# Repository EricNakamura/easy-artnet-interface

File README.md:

# easy-artnet-interface
A open-source project aiming to give access to all people a low budget and easy-to-use artnet-dmx interface node

# 🎭 Professional WT32-ETH01 Art-Net to DMX Node

Um Node Art-Net para DMX512 de alta performance e nível industrial, desenvolvido para a placa **WT32-ETH01 (ESP32 Ethernet)**. 

Este projeto resolve os problemas clássicos de rede em eventos ao vivo: não perde a ligação à internet no seu computador (Mac/Windows), possui **DHCP Inteligente com Auto-Router**, suporte **mDNS**, **proteção contra apagão DMX (40Hz constante)** e **Reset de Fábrica sem botões**.

## 📁 Estrutura do Repositório

| Pasta | Conteúdo |
| :--- | :--- |
| `firmware/` | Sketches por variante de hardware (WT32-ETH01 e ESP32 + W5500) |
| `hub/` | Hub local Rust (descoberta + proxy do painel); ver [hub/README.md](hub/README.md) |
| `src/` | Entradas do PlatformIO; não editar |
| `hardware/kicad/` | Esquema e PCB KiCad |
| `hardware/cad/` | Modelos FreeCAD da caixa |
| `scripts/` | Upload e recuperação por USB |
| `docs/` | [Diagnóstico](docs/diagnostics.md), [recuperação](docs/recovery.md) e [protótipo](docs/prototype.md) |

---

## 🚀 Principais Características

* **Ethernet Fiável:** Baseado no chip LAN8720 (ligação por cabo super estável via UDP).
* **DHCP Inteligente com Auto-Router:**
  * Se ligado a um Router/Switch: obtém IP automaticamente via DHCP.
  * Se ligado direto ao PC/Mac (sem router): **a placa transforma-se num Servidor DHCP automático** (Gama `10.0.0.x`), permitindo ligação imediata *Plug & Play*.
* **Sem Conflito de Internet:** O servidor DHCP interno da placa desativa o envio de Gateway/DNS, permitindo que o Mac/PC continue a usar o Wi-Fi para aceder à internet (WhatsApp, navegação, etc.) enquanto controla a iluminação por cabo.
* **Acesso por Nome (mDNS):** Aceda ao painel via `http://dmx-xxxxxx.local` (o sufixo único aparece no serial e no próprio painel; também pode usar o IP mostrado no painel).
* **Hub local (MVP):** app Rust descobre a interface por mDNS/beacon/scan e abre o painel em `http://localhost:8080/d/<id>/`, sem `.local`/cloud; inclui claim code + HMAC no painel. Ver [hub/README.md](hub/README.md).
* **Painel Web de Configuração:** Interface responsiva para alterar Universo Art-Net, alternar entre DHCP e IP Fixo.
* **Proteção DMX Contínua (40 FPS / 25ms):** Se a rede falhar ou o software de luz fechar, o ESP32 continua a enviar a última cena DMX aos aparelhos, evitando apagões ou piscadelas no palco.
* **Smart Factory Reset:** Reset de fábrica por ciclo de energia (ligar/desligar a placa 2 vezes seguidas rapidamente), eliminando a necessidade de botões físicos.
* **Logging Profissional:** Utiliza o sistema de logs nativo do ESP32 (`log_i`, `log_w`, `log_e`), eliminando o consumo de CPU em produção.

---

## 🛠️ Esquema de Hardware & Pinos

### Componentes Necessários
1. Módulo **WT32-ETH01** (ESP32 com Ethernet).
2. Transcetor RS-485: **Módulo MAX485 padrão** (usado e validado neste projeto).
3. Fêmea XLR 3 pinos ou 5 pinos.
4. Fonte de alimentação 5V DC ou conector USB de escolha.
5. (opcional) Programador esp32 cp2102

> [!WARNING]
> **SOBRE O MÓDULO RS-485**
> O esquema de ligações abaixo foi desenhado e testado especificamente para o **módulo MAX485 clássico**. Se optar por utilizar outros chips (como o SN75176) ou módulos RS-485 isolados de nível industrial, **precisará de adaptar as ligações físicas**. Alguns módulos isolados gerem o sinal de *Enable* automaticamente, o que significa que o pino `EN` (IO04) do ESP32 poderá ter de ser ignorado ou ligado de forma diferente no seu hardware.

### Conexões (WT32-ETH01 ↔ Transcetor MAX485)

| Sinal | Pino WT32-ETH01 | Pino MAX485 | Descrição |
| :--- | :--- | :--- | :--- |
| **TX** | `TXD` | DI (Data In) | Transmissão de dados DMX |
| **EN** | `IO04` | DE / RE | Enable (Habilitar Transmissão) |
| **RX** | `RXD` | RO (Receiver Out)| Reservado / Leitura |
| **VCC** | `5V` | VCC | Alimentação 5V |
| **GND** | `GND` | GND | Terra |

> **Conexão DMX (Saída XLR):** 
> * MAX485 **A** ➔ XLR Pino 3 (DMX +)  
> * MAX485 **B** ➔ XLR Pino 2 (DMX -)  
> * MAX485 **GND** ➔ XLR Pino 1 (Shield / Terra)

---

## 💻 Como Compilar e Enviar o Código

### PlatformIO (recomendado)

O `platformio.ini` já define um ambiente por variante:

| Ambiente | Hardware | Core ESP32 |
| :--- | :--- | :--- |
| `w5500_sem_int` | ESP32 + W5500 (sem fio INT) | 3.x |
| `w5500_com_int` | ESP32 + W5500 (INT no GPIO27) | 2.0.17 |
| `wt32_eth01` | WT32-ETH01 (LAN8720) | 2.0.17 |
| `w5500_diag` | Diagnóstico do W5500 | 3.x |

```bash
pio run -e w5500_sem_int -t upload
pio device monitor
```

### Requisitos (Arduino IDE)

> [!IMPORTANT]
> **VERSÃO DO CORE DO ESP32 OBRIGATÓRIA**
> Este projeto manipula o núcleo de rede a baixo nível para criar o Servidor DHCP. O código foi construído e otimizado para o **ESP32 Core versão 2.x (recomenda-se a 2.0.17)**. 
> Instalar a versão 3.x mais recente no *Boards Manager* causará erros de compilação na variável `dhcps_offer_option`.

1. Instalar o suporte para **ESP32** na Arduino IDE via Boards Manager (`esp32` by Espressif Systems).
2. Selecionar a placa: **ESP32 Dev Module**.
3. Definir a partição de memória: `Huge APP` ou `Default 4MB with spiffs`.
4. **Bibliotecas Externas Necessárias:**
   * `esp_dmx` (por Mitch Weiss) - *Utilizar a versão mais recente.*
   * `ArtnetWifi` (por Hideaki Tai) - *Utilizar a versão mais recente.*

### Configuração do Debug / Logs
Em **Ferramentas (Tools) > Core Debug Level**:
* Escolha `Info` ou `Debug` durante os testes.
* Escolha `None` ao gravar a versão final de produção para desempenho máximo.

---

## 📖 Guia de Utilização

### 1. Primeiro Arranque (Plug & Play)
1. Ligue o cabo Ethernet entre a placa e o seu computador (ou Switch).
2. Abra o navegador web e aceda ao endereço mostrado no serial/painel: **`http://dmx-xxxxxx.local`** (sufixo único do chip), ou use o IP indicado.
3. Configure o Universo Art-Net pretendido (Padrão: `0`).

### 2. Softwares Recomendados

> [!TIP]
> **🌟 EDIÇÃO ESPECIAL QLC+ (Recomendado)**
> Disponibilizamos uma versão customizada (Fork) do **QLC+** otimizada especificamente para trabalhar em perfeita harmonia com este Node. Se procura a melhor experiência de uso e estabilidade, descarregue a nossa versão aqui:
> 👉 **[Download da Nossa Fork do QLC+](https://github.com/EricNakamura/qlcplus-LEGACY)**

O Node funciona com qualquer software compatível com o protocolo Art-Net I, II, III ou IV:
* **QLC+**
* **Lumikit**
* **Resolume Arena**
* **GrandMA2 / GrandMA3 (onPC)**
* **Onyx (Obsidian)**
* **MadMapper / Chamsys / FreeStyler**

### 3. Reset de Fábrica (Factory Reset)
Se perder o acesso ao IP ou configurar uma rede incorreta:
1. Ligue a placa à energia.
2. Assim que o LED piscar, desligue da tomada.
3. Repita este processo **2 vezes consecutivas** (em menos de 4 segundos em cada tentativa).
4. Na 2ª vez, deixe a placa ligada: a memória interna será apagada e o sistema voltará aos padrões de fábrica (DHCP ativo e rede `10.0.0.1` em fallback).

---

## 📜 Licença

Este projeto é um software livre distribuído sob os termos da GNU General Public License v3.0 (GPLv3).

**Para mais informações consultar o ficheiro [LICENSE](LICENSE)**

---
*Desenvolvido com foco em alta performance e fiabilidade para eventos ao vivo.*

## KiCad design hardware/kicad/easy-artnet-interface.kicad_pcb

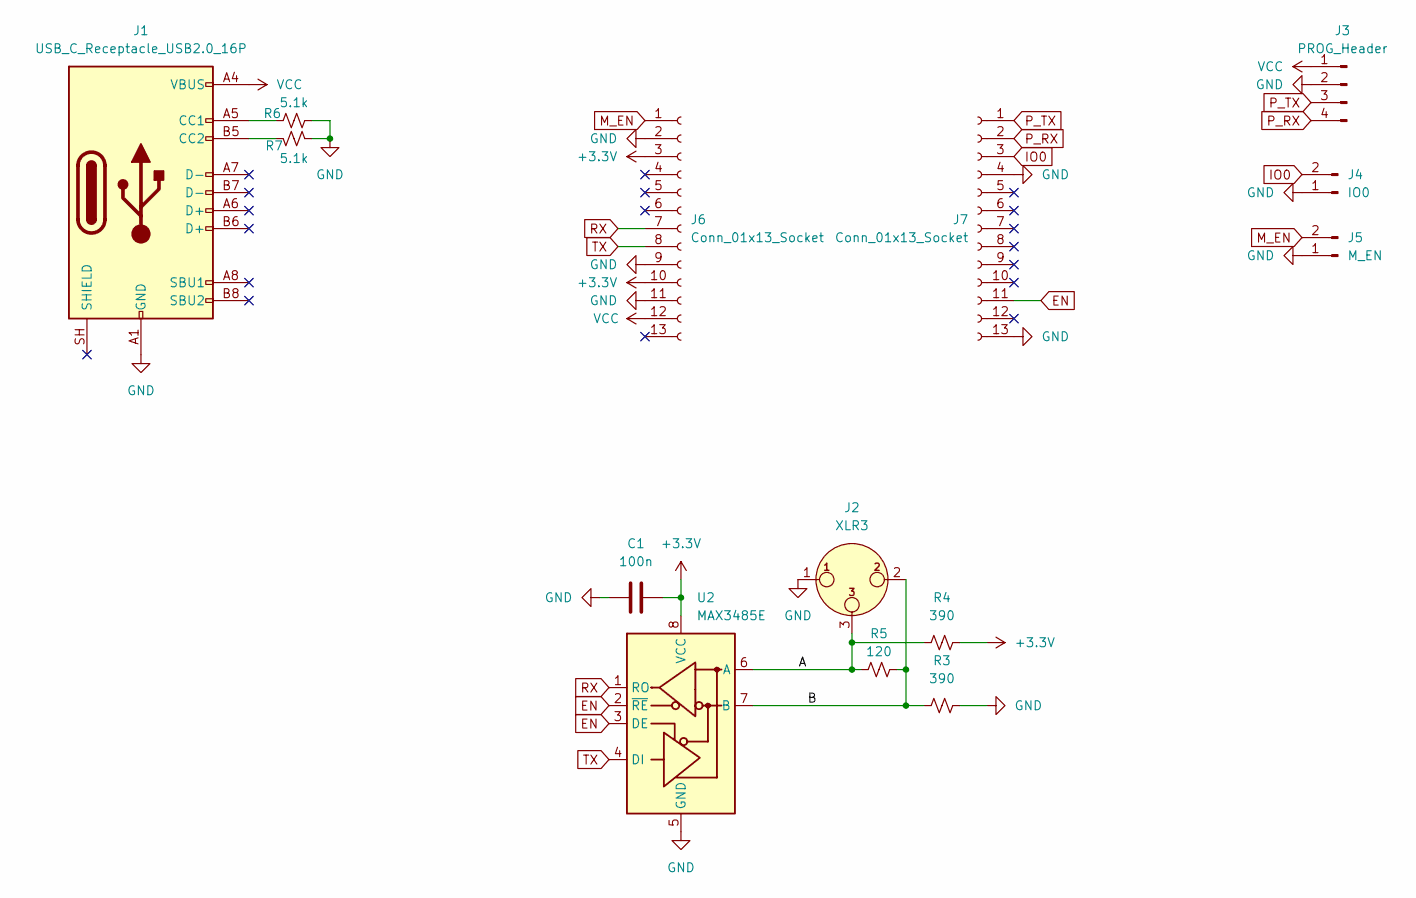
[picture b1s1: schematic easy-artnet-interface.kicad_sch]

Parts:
C1: 100n; C_0805_2012Metric_Pad1.18x1.45mm_HandSolder
J1: USB_C_Receptacle_USB2.0_16P; USB_C_Receptacle_G-Switch_GT-USB-7010ASV
J2: XLR3; PinHeader_1x03_P2.54mm_Vertical
J3: PROG_Header; PinHeader_1x04_P2.54mm_Vertical
J4: IO0; PinHeader_1x02_P2.54mm_Vertical
J5: M_EN; PinHeader_1x02_P2.54mm_Vertical
J6, J7: Conn_01x13_Socket; PinHeader_1x13_P2.54mm_Vertical
R3, R4: 390; R_0805_2012Metric_Pad1.20x1.40mm_HandSolder
R5: 120; R_0805_2012Metric_Pad1.20x1.40mm_HandSolder
R6, R7: 5.1k; R_0805_2012Metric_Pad1.20x1.40mm_HandSolder
U2: MAX3485E; SOP-8_3.76x4.96mm_P1.27mm

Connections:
+3.3V: C1.2, J6.3, J6.10, R4.2, U2.8 (VCC)
/A: J2.3, R4.1, R5.1, U2.6 (A)
/B: J2.2, R3.1, R5.2, U2.7 (B)
EN: J7.11, U2.2 (~RE), U2.3 (DE)
GND: C1.1, J1.A1 (GND), J1.A12 (GND), J1.B1 (GND), J1.B12 (GND), J2.1, J3.2, J4.1, J5.1, J6.2, J6.9, J6.11, J7.4, J7.13, R3.2, R6.2, R7.1, U2.5 (GND)
IO0: J4.2, J7.3
M_EN: J5.2, J6.1
unnamed: J1.A5 (CC1), R6.1
unnamed: J1.B5 (CC2), R7.2
P_RX: J3.4, J7.2
P_TX: J3.3, J7.1
RX: J6.7, U2.1 (RO)
TX: J6.8, U2.4 (DI)
VCC: J1.A4 (VBUS), J1.A9 (VBUS), J1.B4 (VBUS), J1.B9 (VBUS), J3.1, J6.12

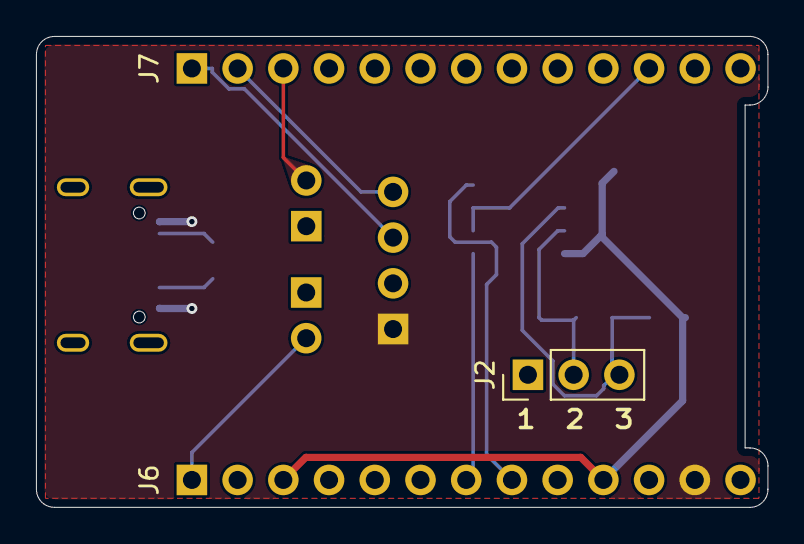
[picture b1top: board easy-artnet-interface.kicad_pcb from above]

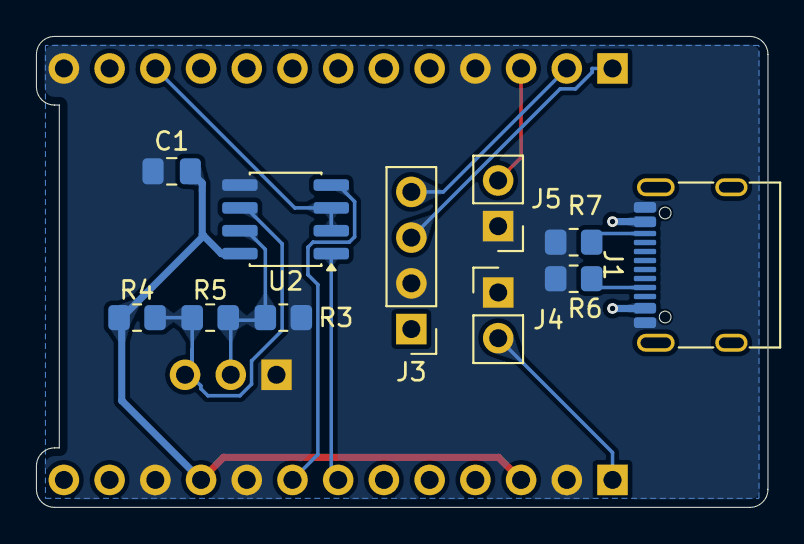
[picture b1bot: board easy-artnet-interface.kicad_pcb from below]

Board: 2 copper layers, 40.6 x 26.2 mm, 14 parts (11 on the bottom side), 14 nets.

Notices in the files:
README.md:
License: GPLv3
